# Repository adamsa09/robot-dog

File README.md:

# Servo-driven Quadruped Robot
Adam Sarhan &  Lucas Dauth

[Math](./report.pdf)

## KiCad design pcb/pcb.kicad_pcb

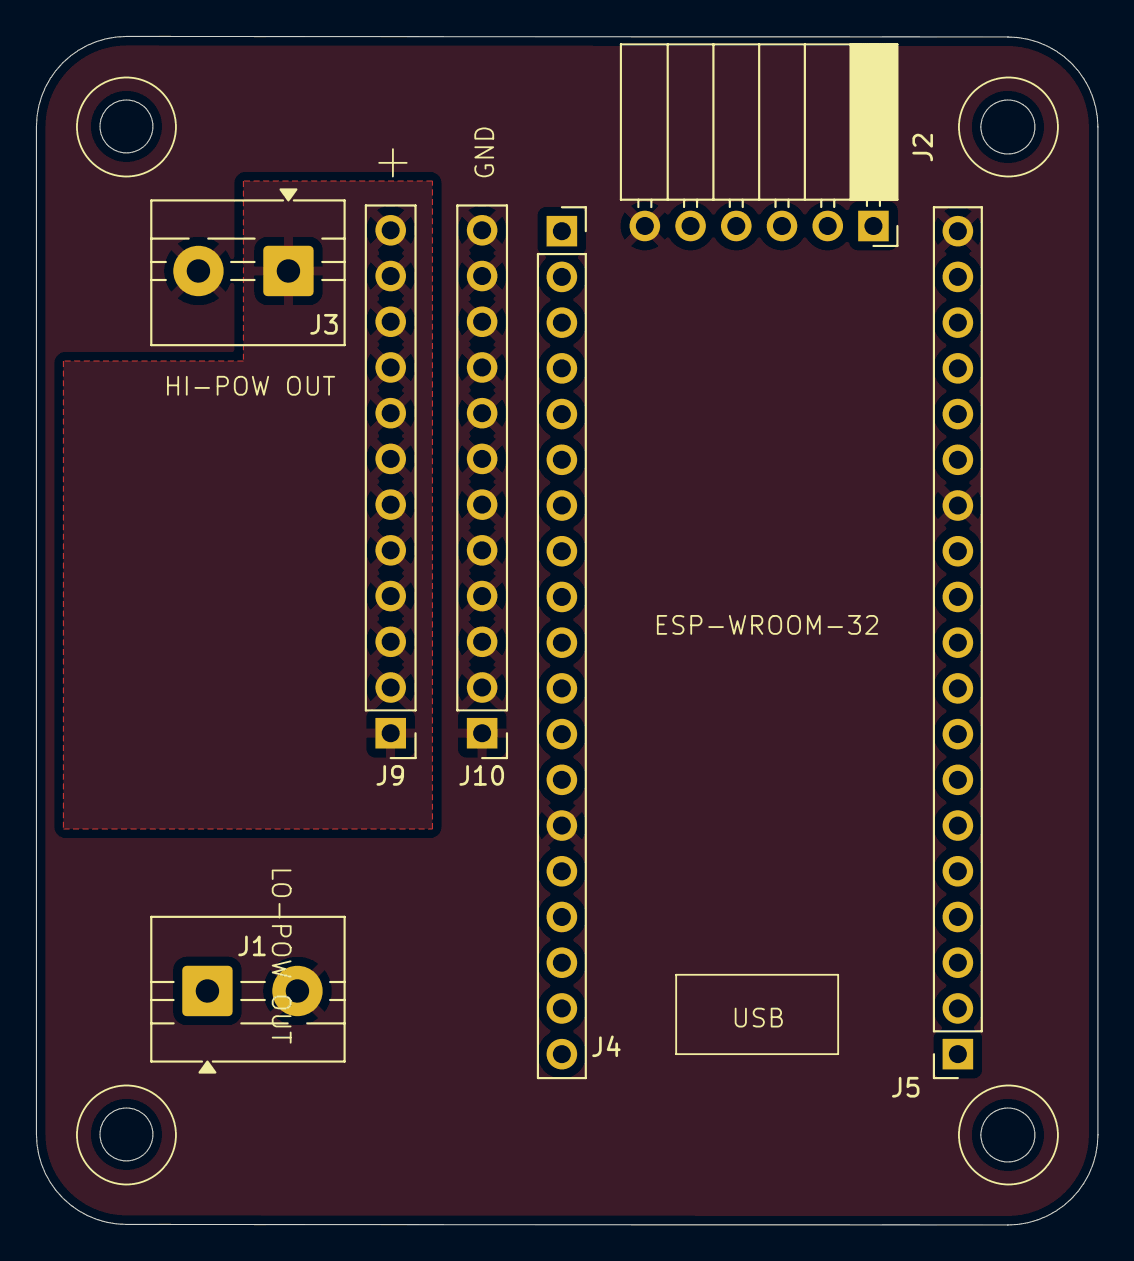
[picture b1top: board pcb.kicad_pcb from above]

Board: 2 copper layers, 59.0 x 66.0 mm, 7 parts (0 on the bottom side), 5 nets, no tracks yet.

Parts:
J1: LM2596 OUTPUT; TerminalBlock_MaiXu_MX126-5.0-02P_1x02_P5.00mm
J2: PCA9685; PinSocket_1x06_P2.54mm_Horizontal
J3: 20A 300W High-Power Buck Converter OUTPUT; TerminalBlock_MaiXu_MX126-5.0-02P_1x02_P5.00mm
J4: ESP32_1; PinSocket_1x19_P2.54mm_Vertical
J5: ESP32_2; PinSocket_1x19_P2.54mm_Vertical
J9: Servo +; PinHeader_1x12_P2.54mm_Vertical
J10: Servo -; PinHeader_1x12_P2.54mm_Vertical

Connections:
+5V: J1.1, J2.2, J4.19
+6.8V: J3.1, J9.1, J9.2, J9.3, J9.4, J9.5, J9.6, J9.7, J9.8, J9.9, J9.10, J9.11, J9.12
GND: J1.2, J2.6, J3.2, J4.14, J5.13, J5.19, J10.1, J10.2, J10.3, J10.4, J10.5, J10.6, J10.7, J10.8, J10.9, J10.10, J10.11, J10.12
unnamed: J2.3, J5.14
unnamed: J2.4, J5.17

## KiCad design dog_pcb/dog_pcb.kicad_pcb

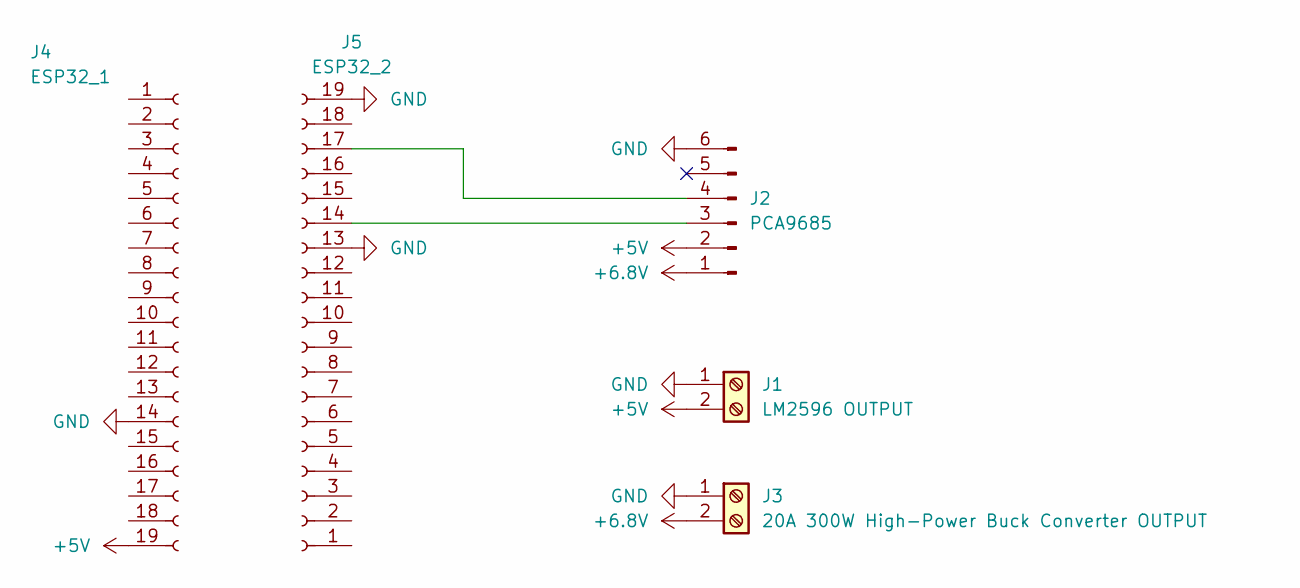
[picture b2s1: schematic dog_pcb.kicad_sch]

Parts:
J1: LM2596 OUTPUT; Altech_AK100_1x02_P5.00mm
J2: PCA9685; PinHeader_1x06_P2.54mm_Vertical
J3: 20A 300W High-Power Buck Converter OUTPUT; Altech_AK100_1x02_P5.00mm
J4: ESP32_1; PinHeader_1x19_P2.54mm_Vertical
J5: ESP32_2; PinHeader_1x19_P2.54mm_Vertical

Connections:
+5V: J1.2, J2.2, J4.19
+6.8V: J2.1, J3.2
GND: J1.1, J2.6, J3.1, J4.14, J5.13, J5.19
unnamed: J2.3, J5.14
unnamed: J2.4, J5.17

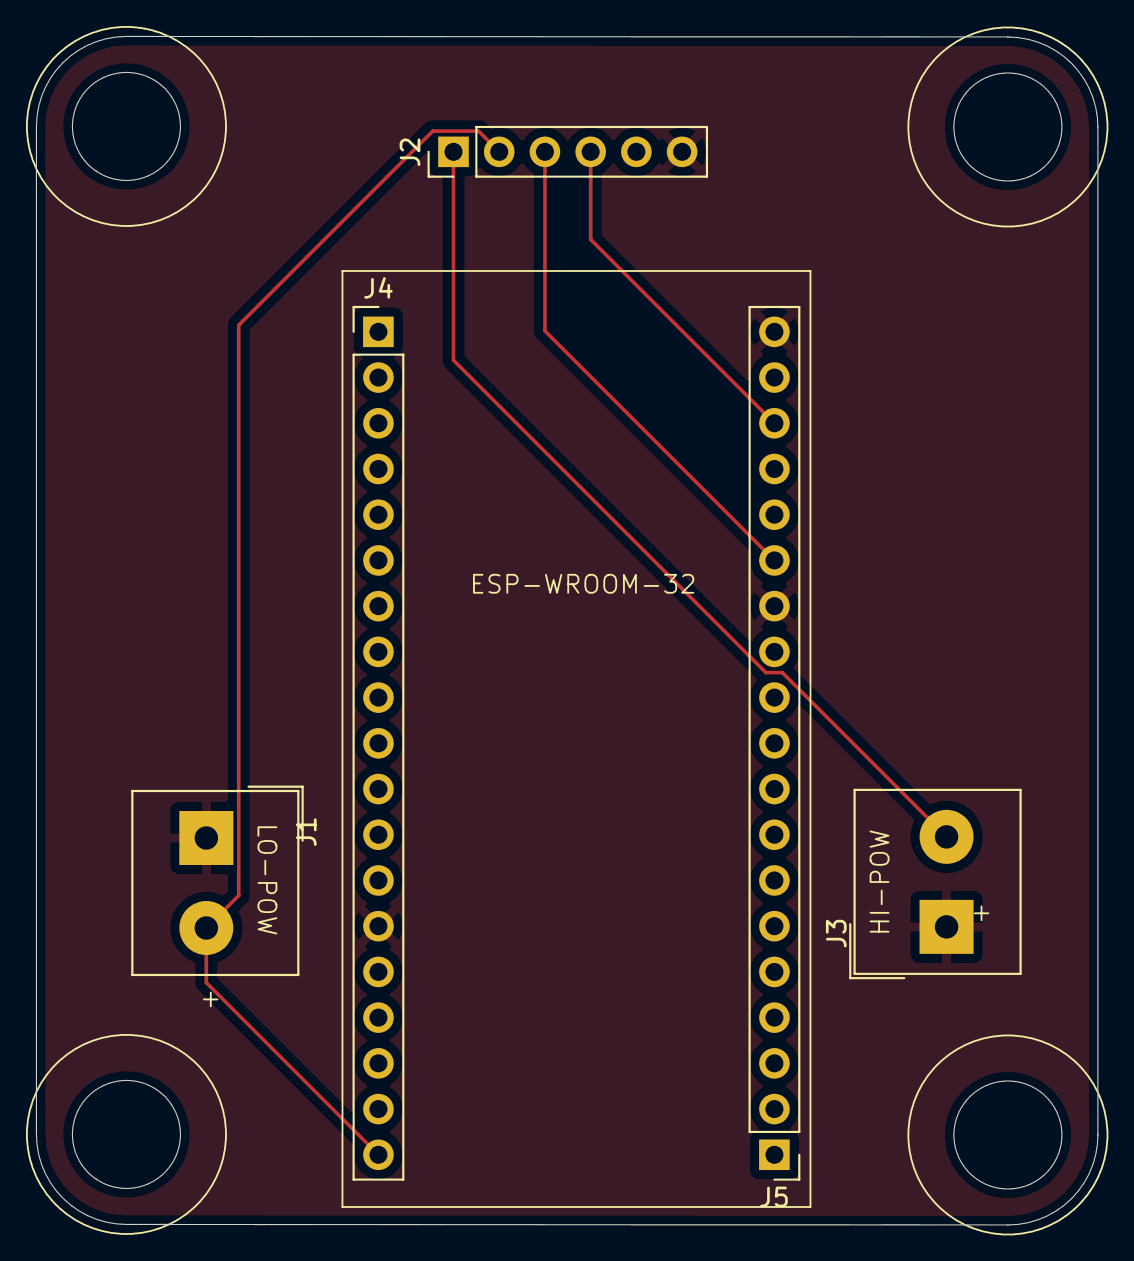
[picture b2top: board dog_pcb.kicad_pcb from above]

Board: 2 copper layers, 59.0 x 66.0 mm, 5 parts (0 on the bottom side), 5 nets.

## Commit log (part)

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2026-03-11 Add 3D models to footprints in PCB for screw terminals and female pin sockets.
2026-03-11 Add .DS_Store to .gitignore
2026-03-16 Working gait with linear interpolation at ./gait-lerp
2026-03-17 Add: PS5 controller support, homing command, per-joint calibration.
2026-03-18 Modify power management on PCB. Battery, high power buck converter I/O & low power buck converter input remain off board. Reduce screw hole size.
2026-03-18 Add detailed math write-up
2026-03-18 Fix: Add dedicated 6.8V copper fill to PCB where a 1x12 header pin is used to power servos. Fixes bottleneck of using the PCA9685 chip to power the servos (doesn't allow for 20A stall current due to 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
2026-03-18 Fix: short caused by screw terminal's GND being in 6.8V copper fill. Rearrange components to better integrate in CAD.
2026-03-18 Move code to ./code and rename gait-lerp to trot, which will be the definitive firmware for the dog.
2026-03-18 Rename code/trot to code/firmware
2026-03-18 Add CAD screenshot to README
2026-03-20 Add clarification on IK for a 4 bar linkage
2026-03-22 Migrate codebase to PlatformIO
